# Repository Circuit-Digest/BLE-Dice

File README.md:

# [BLE-Dice](https://circuitdigest.com/microcontroller-projects/how-to-build-a-smart-led-dice)
An electronics dice with BluetoothLE connectivity.

<br>

<br>

<br>

[<h1>Click here](https://circuitdigest.com/tags/ESP32) For other ESP32 tutorials.</h1>

<br>
<br>
<br>

<br>
[Note: As this project is very simple we are only providing the code, schematic, and a few essential images if you want to get the images or code explanations do check out the Circuit Digest website.
<br>
<br>

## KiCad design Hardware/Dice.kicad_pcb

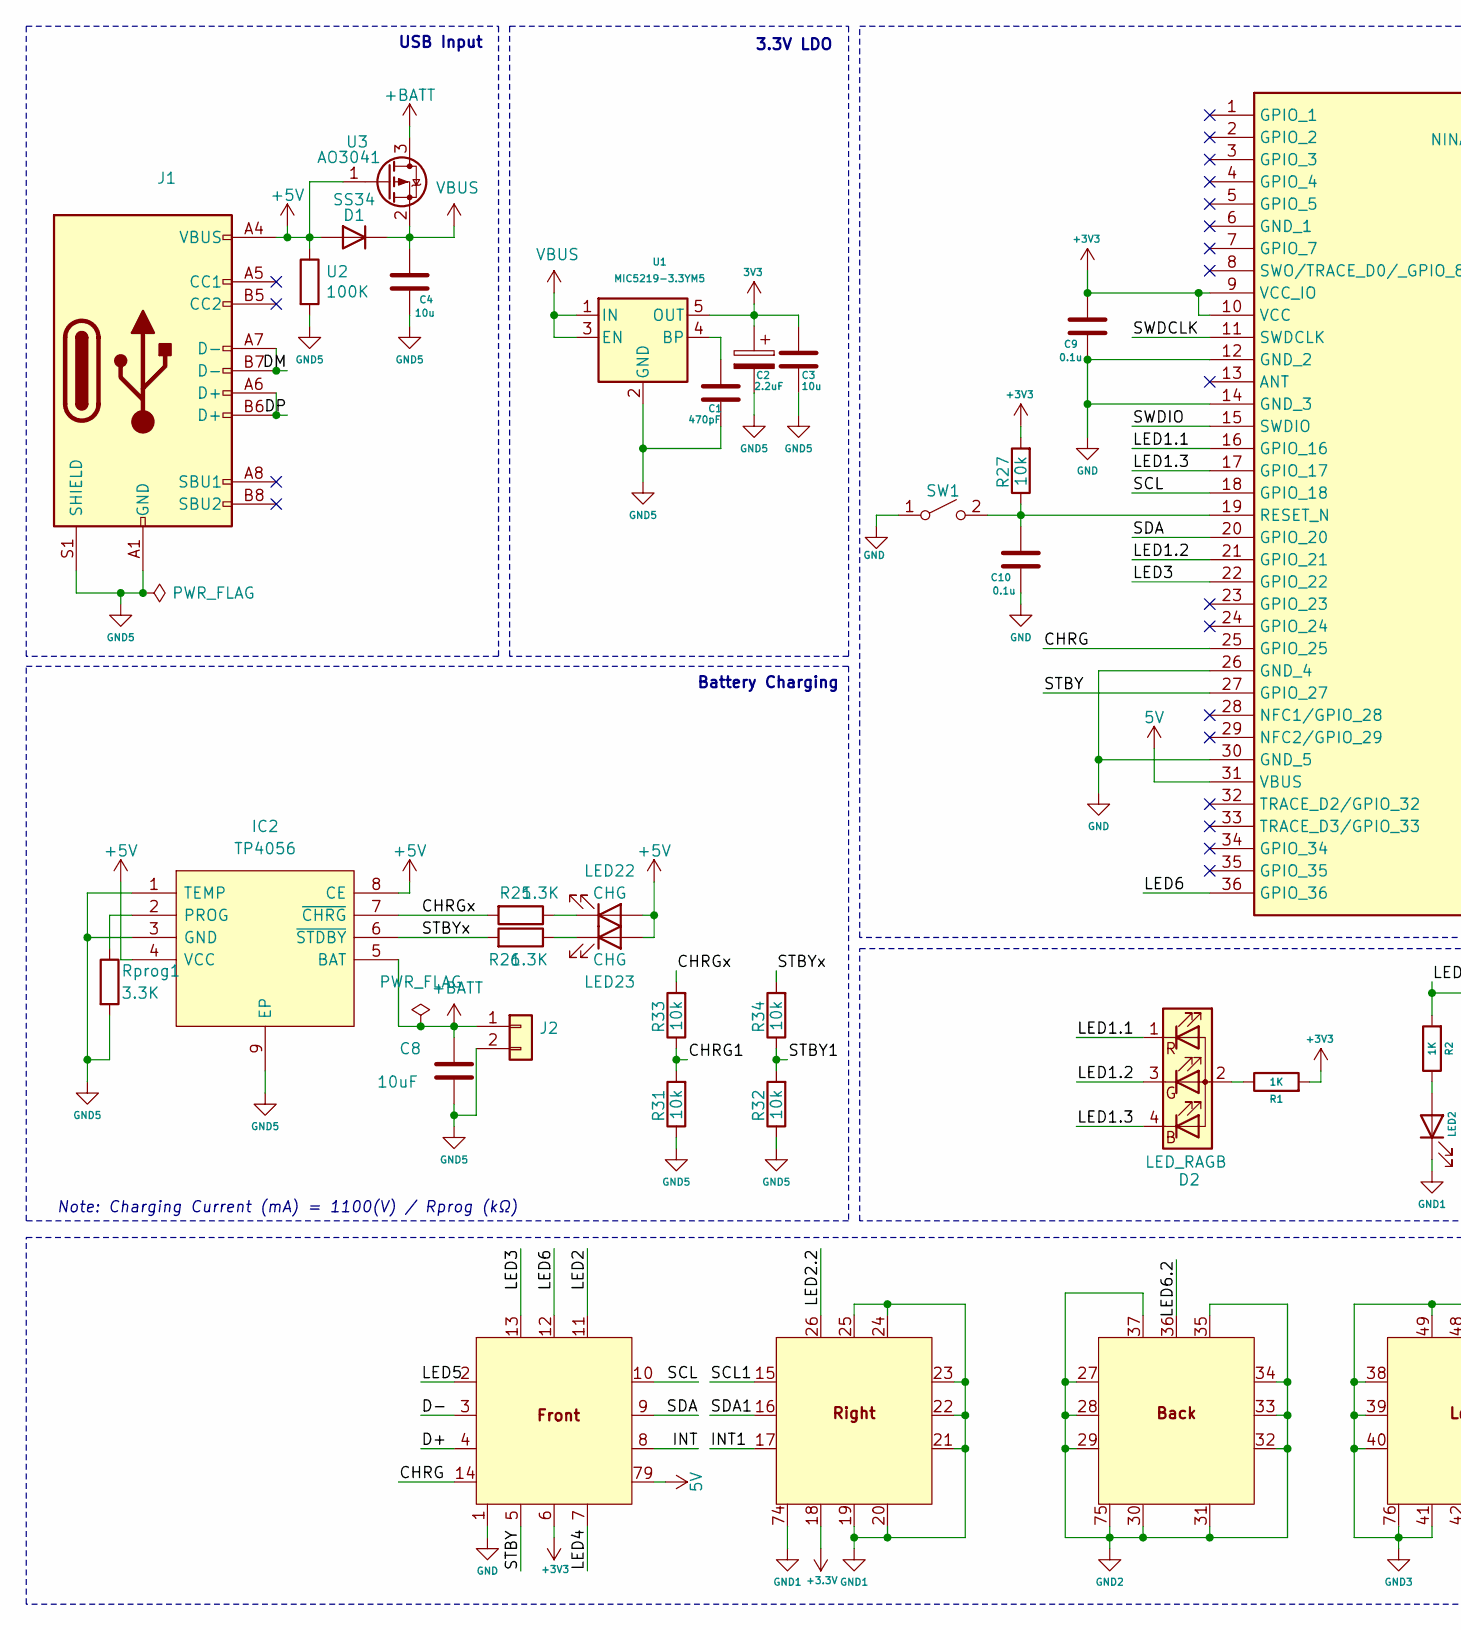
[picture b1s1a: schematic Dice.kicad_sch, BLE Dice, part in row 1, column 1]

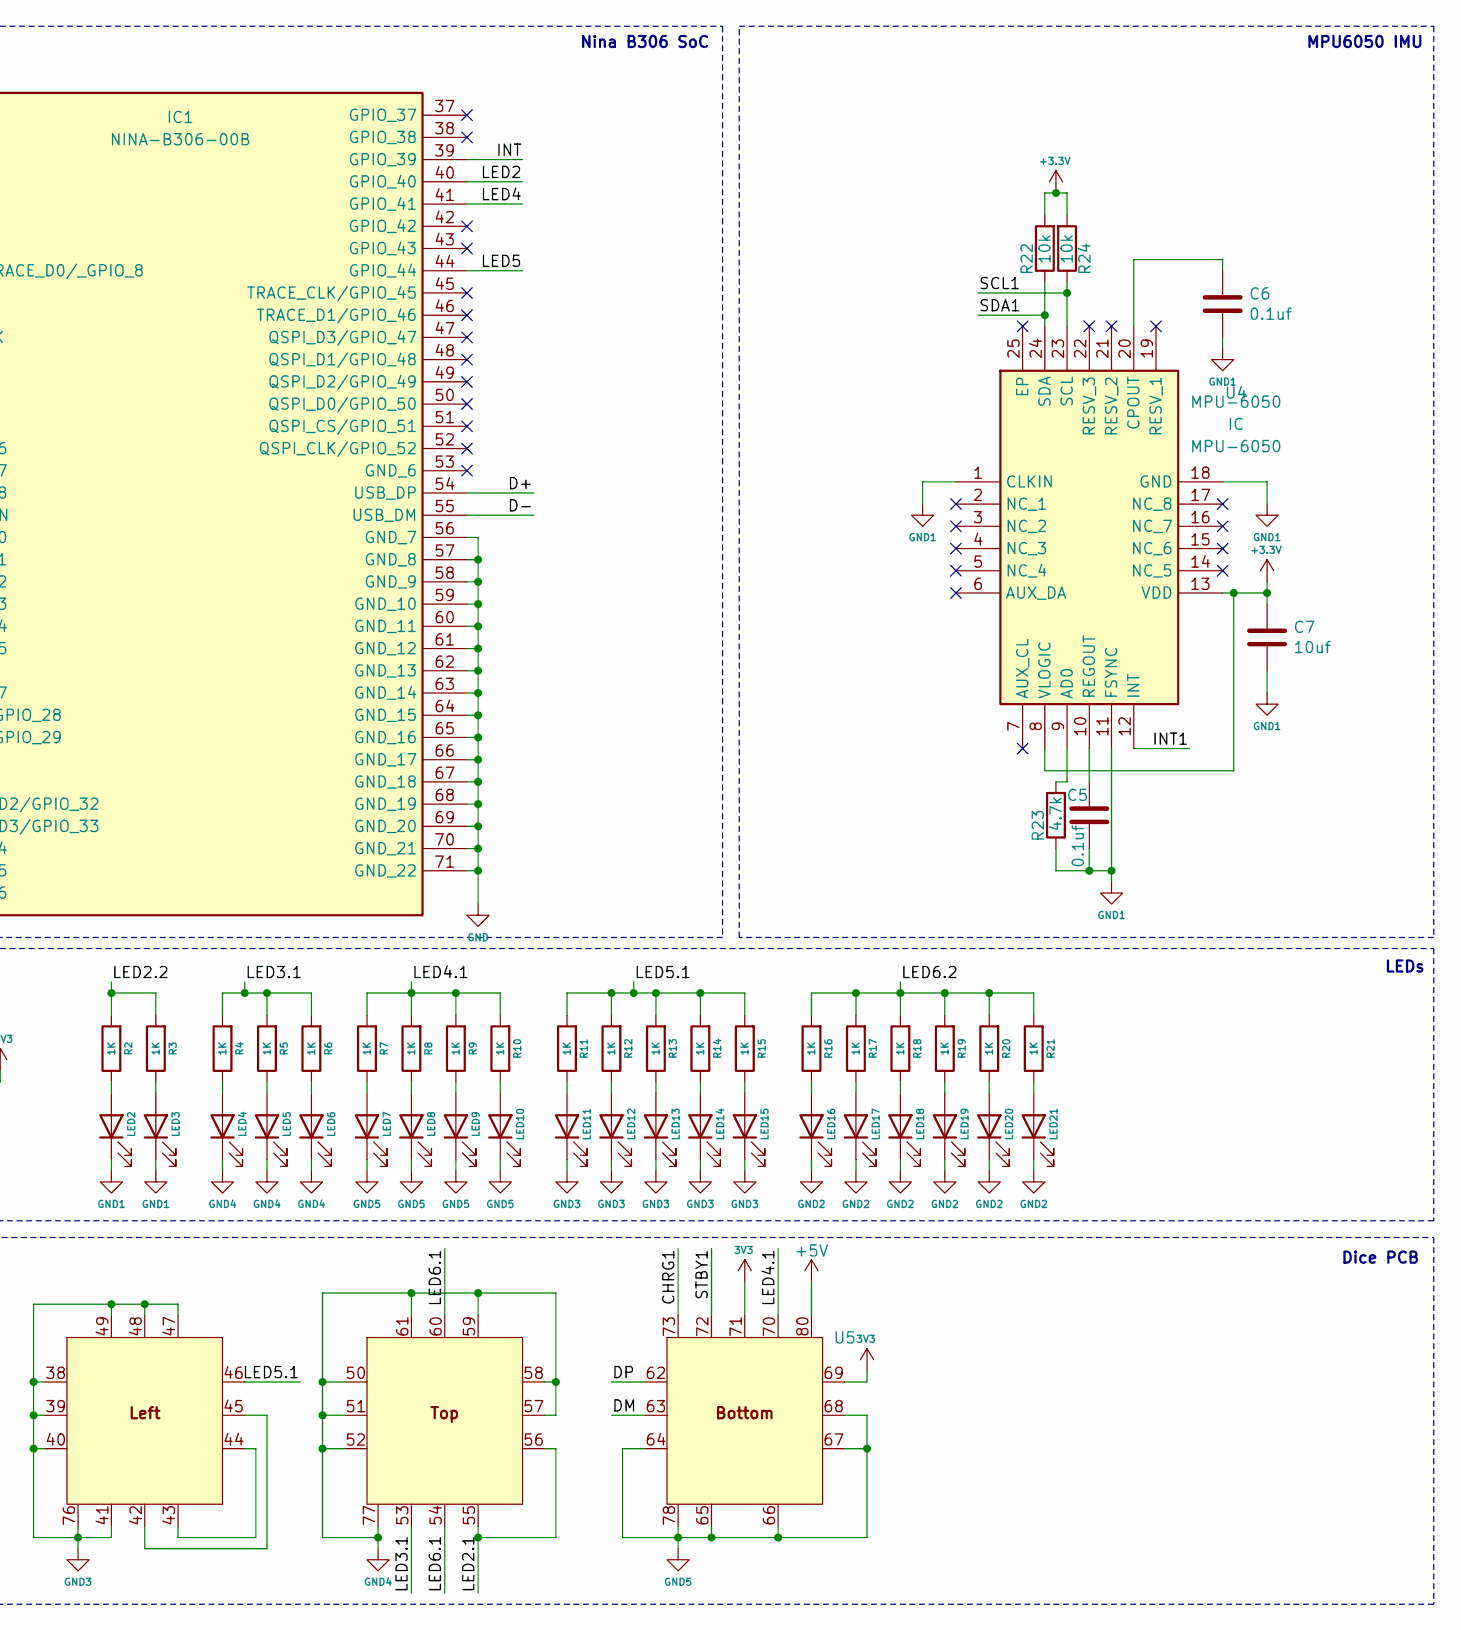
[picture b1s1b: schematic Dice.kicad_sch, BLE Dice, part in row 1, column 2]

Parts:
C1: 470pF; C_0603_1608Metric
C2: 2.2uF; C_0805_2012Metric
C3, C4: 10u; C_0603_1608Metric
C5, C6: 0.1uf; C_0603_1608Metric
C7: 10uf; C_0603_1608Metric
C8: 10uF; C_0603_1608Metric
C9, C10: 0.1u; C_0603_1608Metric
D1: SS34; D_SMA
D2: LED_RAGB; LED-ARRAY-SMD_4P-L1.6-W1.5-BR_XL-1615RGBC-RF
IC1: NINA-B306-00B; NINAB30600B; Mouser Part Number 377-NINA-B306-00B
IC2: TP4056; SOIC127P600X175-9N; Manufacturer_Part_Number TP4056-42-ESOP8
J1: USB_C_Receptacle_USB2.0; USB_C_Receptacle_HRO_TYPE-C-31-M-12
J2: B2B-PH-SM4-TB(LF)(SN); PinSocket_1x02_P2.00mm_Vertical_SMD_Pin1Right
LED2, LED3, LED4, LED5, LED6, LED7, LED8, LED9, LED10, LED11, LED12, LED13, LED14, LED15, LED16, LED17, LED18, LED19, LED20, LED21: POW_LED; LED_0805_2012Metric
LED22, LED23: CHG; LED_0603_1608Metric
R1, R2, R3, R4, R5, R6, R7, R8, R9, R10, R11, R12, R13, R14, R15, R16, R17, R18, R19, R20, R21: 1K; R_0603_1608Metric
R22, R24, R27, R31, R32, R33, R34: 10k; R_0603_1608Metric
R23: 4.7k; R_0603_1608Metric
R25, R26: 1.3K; R_0603_1608Metric
Rprog1: 3.3K; R_0603_1608Metric
SW1: TS-1088R-02526; Tactile 3x4x2mm TS-A010
U1: MIC5219-3.3YM5; SOT-23-5
U2: 100K; R_0603_1608Metric
U3: AO3041; SOT-23
U4: MPU-6050; MPU6050; Mouser Part Number 410-MPU-6050
U5: Cube

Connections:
3V3: C2.1, C3.1, U1.5 (OUT), U5.69, U5.71
5V: IC1.31 (VBUS), U5.79
+3.3V: C7.1, R22.2, R24.2, U4.8 (VLOGIC), U4.13 (VDD), U5.18
+3V3: C9.1, IC1.9 (VCC_IO), IC1.10 (VCC), R1.2, R27.2, U5.6
+5V: D1.2 (A), IC2.4 (VCC), IC2.8 (CE), J1.A4 (VBUS), J1.A9 (VBUS), J1.B4 (VBUS), J1.B9 (VBUS), LED22.2 (A), LED23.2 (A), U2.1, U3.1 (G), U5.80
+BATT: C8.1, IC2.5 (BAT), J2.1, U3.3 (D)
/CHRG: IC1.25 (GPIO_25), U5.14
/CHRG1: R31.2, R33.1, U5.73
/CHRGx: IC2.7 (~CHRG), R25.2, R33.2
/D+: IC1.54 (USB_DP), U5.4
/D-: IC1.55 (USB_DM), U5.3
/DM: J1.A7 (D-), J1.B7 (D-), U5.63
/DP: J1.A6 (D+), J1.B6 (D+), U5.62
/INT: IC1.39 (GPIO_39), U5.8
/INT1: U4.12 (INT), U5.17
/LED1.1: D2.1 (RK), IC1.16 (GPIO_16)
/LED1.2: D2.3 (GK), IC1.21 (GPIO_21)
/LED1.3: D2.4 (BK), IC1.17 (GPIO_17)
/LED2: IC1.40 (GPIO_40), U5.11
/LED2.1: U5.55, U5.56
/LED2.2: R2.2, R3.2, U5.26
/LED3: IC1.22 (GPIO_22), U5.13
/LED3.1: R4.2, R5.2, R6.2, U5.53
/LED4: IC1.41 (GPIO_41), U5.7
/LED4.1: R7.2, R8.2, R9.2, R10.2, U5.70
/LED5: IC1.44 (GPIO_44), U5.2
/LED5.1: R11.2, R12.2, R13.2, R14.2, R15.2, U5.46
/LED6: IC1.36 (GPIO_36), U5.12
/LED6.1: U5.54, U5.60
/LED6.2: R16.2, R17.2, R18.2, R19.2, R20.2, R21.2, U5.36
/SCL: IC1.18 (GPIO_18), U5.10
/SCL1: R24.1, U4.23 (SCL), U5.15
/SDA: IC1.20 (GPIO_20), U5.9
/SDA1: R22.1, U4.24 (SDA), U5.16
/STBY: IC1.27 (GPIO_27), U5.5
/STBY1: R32.2, R34.1, U5.72
/STBYx: IC2.6 (~STDBY), R26.2, R34.2
/SWDCLK: IC1.11 (SWDCLK)
/SWDIO: IC1.15 (SWDIO)
GND: C9.2, C10.2, IC1.12 (GND_2), IC1.14 (GND_3), IC1.26 (GND_4), IC1.30 (GND_5), IC1.56 (GND_7), IC1.57 (GND_8), IC1.58 (GND_9), IC1.59 (GND_10), IC1.60 (GND_11), IC1.61 (GND_12), IC1.62 (GND_13), IC1.63 (GND_14), IC1.64 (GND_15), IC1.65 (GND_16), IC1.66 (GND_17), IC1.67 (GND_18), IC1.68 (GND_19), IC1.69 (GND_20), IC1.70 (GND_21), IC1.71 (GND_22), SW1.1 (A), U5.1
GND1: C5.2, C6.2, C7.2, LED2.1 (K), LED3.1 (K), R23.1, U4.1 (CLKIN), U4.11 (FSYNC), U4.18 (GND), U5.19, U5.20, U5.21, U5.22, U5.23, U5.24, U5.25, U5.74
GND2: LED16.1 (K), LED17.1 (K), LED18.1 (K), LED19.1 (K), LED20.1 (K), LED21.1 (K), U5.27, U5.28, U5.29, U5.30, U5.31, U5.32, U5.33, U5.34, U5.35, U5.37, U5.75
GND3: LED11.1 (K), LED12.1 (K), LED13.1 (K), LED14.1 (K), LED15.1 (K), U5.38, U5.39, U5.40, U5.41, U5.47, U5.48, U5.49, U5.76
GND4: LED4.1 (K), LED5.1 (K), LED6.1 (K), U5.50, U5.51, U5.52, U5.57, U5.58, U5.59, U5.61, U5.77
GND5: C1.2, C2.2, C3.2, C4.2, C8.2, IC2.1 (TEMP), IC2.3 (GND), IC2.9 (EP), J1.A1 (GND), J1.A12 (GND), J1.B1 (GND), J1.B12 (GND), J1.S1 (SHIELD), J2.2, LED7.1 (K), LED8.1 (K), LED9.1 (K), LED10.1 (K), R31.1, R32.1, Rprog1.2, U1.2 (GND), U2.2, U5.64, U5.65, U5.66, U5.67, U5.68, U5.78
unnamed: D2.2 (A), R1.1
unnamed: C10.1, IC1.19 (RESET_N), R27.1, SW1.2 (B)
unnamed: IC2.2 (PROG), Rprog1.1
unnamed: LED2.2 (A), R2.1
unnamed: LED3.2 (A), R3.1
unnamed: LED4.2 (A), R4.1
unnamed: LED5.2 (A), R5.1
unnamed: LED6.2 (A), R6.1
unnamed: LED7.2 (A), R7.1
unnamed: LED8.2 (A), R8.1
unnamed: LED9.2 (A), R9.1
unnamed: LED10.2 (A), R10.1
unnamed: LED11.2 (A), R11.1
unnamed: LED12.2 (A), R12.1
unnamed: LED13.2 (A), R13.1
unnamed: LED14.2 (A), R14.1
unnamed: LED15.2 (A), R15.1
unnamed: LED16.2 (A), R16.1
unnamed: LED17.2 (A), R17.1
unnamed: LED18.2 (A), R18.1
unnamed: LED19.2 (A), R19.1
unnamed: LED20.2 (A), R20.1
unnamed: LED21.2 (A), R21.1
unnamed: LED22.1 (K), R25.1
unnamed: LED23.1 (K), R26.1
unnamed: C1.1, U1.4 (BP)
unnamed: R23.2, U4.9 (AD0)
unnamed: C6.1, U4.20 (CPOUT)
unnamed: C5.1, U4.10 (REGOUT)
unnamed: U5.42, U5.45
unnamed: U5.43, U5.44
VBUS: C4.1, D1.1 (K), U1.1 (IN), U1.3 (EN), U3.2 (S)

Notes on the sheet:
Nina B306 SoC
MPU6050 IMU
Note: Charging Current (mA) = 1100(V) / Rprog (kΩ)
Battery Charging
USB Input
3.3V LDO
LEDs
Dice PCB

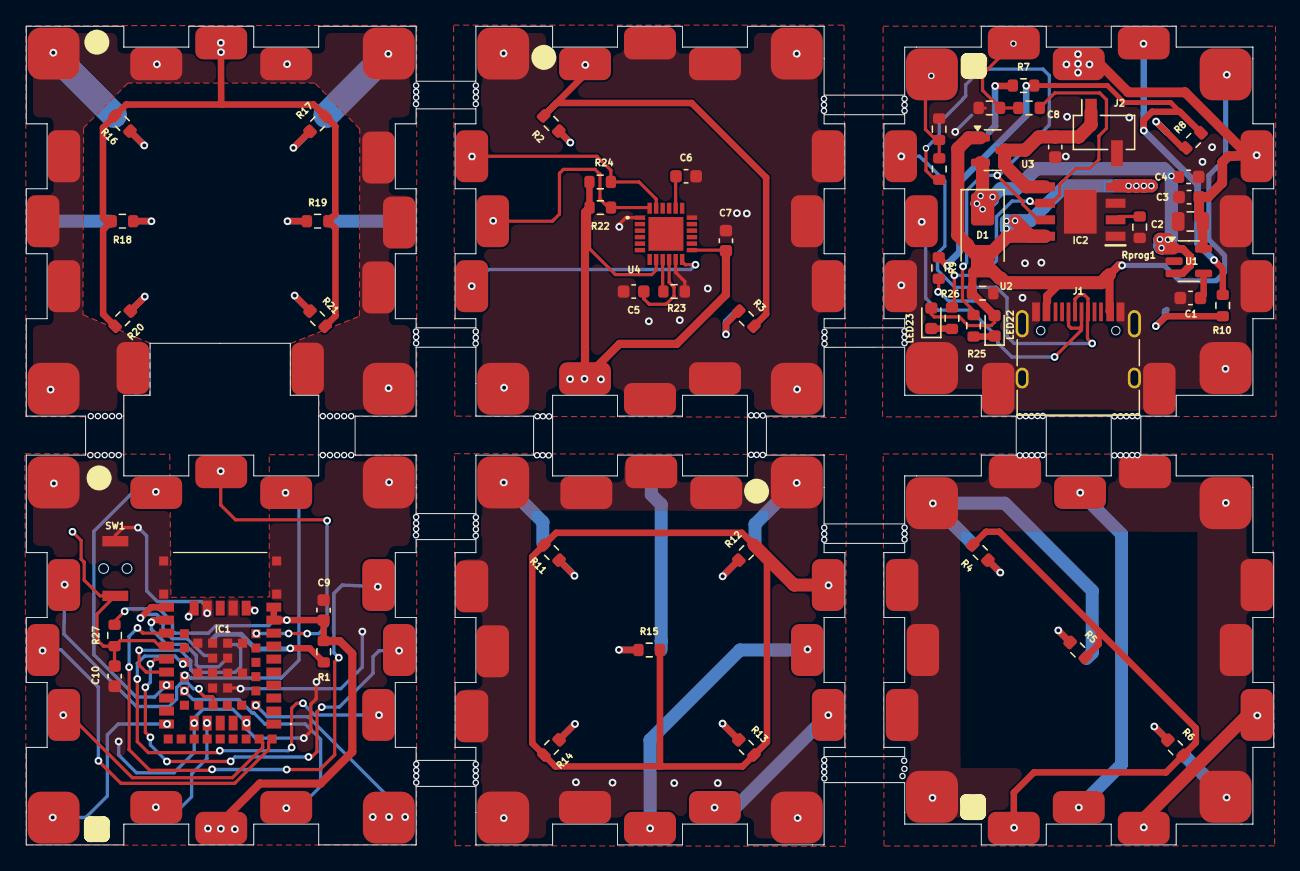
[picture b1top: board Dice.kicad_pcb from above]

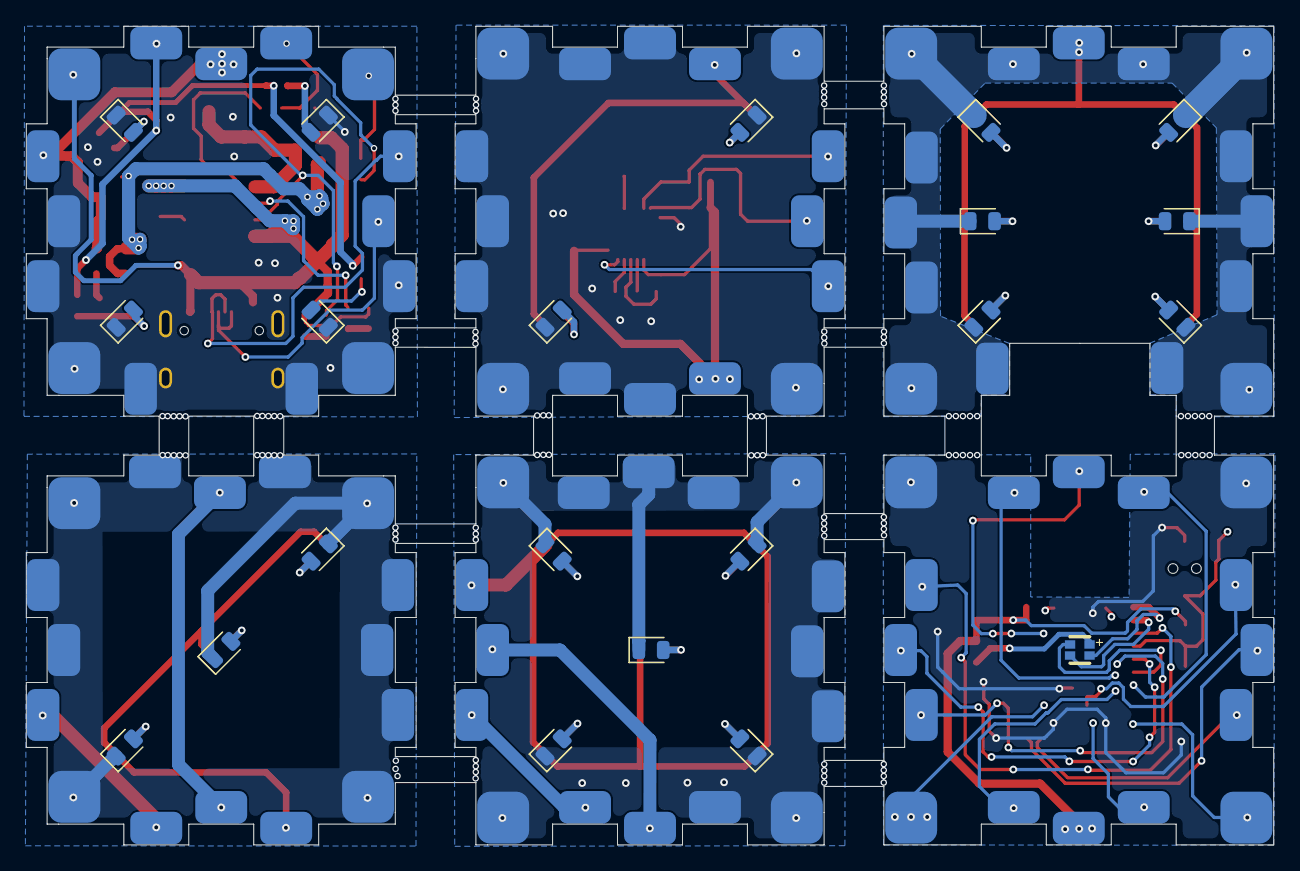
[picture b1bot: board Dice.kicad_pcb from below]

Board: 2 copper layers, 96.0 x 63.0 mm, 76 parts (21 on the bottom side), 75 nets.

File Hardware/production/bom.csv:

Designator,Footprint,Quantity,Value,LCSC Part #
C1,0603,1,470pF,
"C10, C9",0603,2,0.1u,
C2,0805,1,2.2uF,
"C3, C4",0603,2,10u,
"C5, C6",0603,2,0.1uf,
"C7, C8",0603,2,10uf,
D1,D_SMA,1,SS34,
D2,LED-ARRAY-SMD_4P-L1.6-W1.5-BR_XL-1615RGBC-RF,1,LED_RAGB,
IC1,NINAB30600B,1,NINA-B306-00B,
IC2,SOIC127P600X175-9N,1,TP4056,
J1,USB_C_Receptacle_HRO_TYPE-C-31-M-12,1,USB_C_Receptacle_USB2.0,
J2,PinSocket_1x02_P2.00mm_Vertical_SMD_Pin1Right,1, B2B-PH-SM4-TB(LF)(SN) ,
"LED10, LED11, LED12, LED13, LED14, LED15, LED16, LED17, LED18, LED19, LED2, LED20, LED21, LED3, LED4, LED5, LED6, LED7, LED8, LED9",0805,20,POW_LED,
"LED22, LED23",0603,2,CHG,
"R1, R10, R11, R12, R13, R14, R15, R16, R17, R18, R19, R2, R20, R21, R3, R4, R5, R6, R7, R8, R9",0603,21,1K,
"R22, R24, R27, R31, R32, R33, R34",0603,7,10k,
R23,0603,1,4.7k,
"R25, R26",0603,2,1.3K,
Rprog1,0603,1,3.3K,
SW1,Tactile 3x4x2mm TS-A010,1,TS-1088R-02526 ,
U1,SOT-23-5,1,MIC5219-3.3YM5,
U2,0603,1,100K,
U3,SOT-23,1,AO3041,
U4,MPU6050,1,MPU-6050,
U5,Cube,1,~,
